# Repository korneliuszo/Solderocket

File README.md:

# Solderocket
Regular solder paste dispensers must be connected to compressed air which you can provide with huge compressor. As a maker I can not run a large compressor in my room because of its noise and footprint.

Stencils might be a solution but for small size PCB work they are too dirty and I don't like to touch the chemical solder paste with my hands and tools. It takes more time to clean up every time than apply it to the PCB.

That's why I decided to design a desktop solder paste dispenser that is clean, easy to use and small in size. I call it Solderocket.

Using the rotary knobs, the time and pressure can be set so that the right dot size can be selected for each type of solder paste.

This device is indispensable when working with SMD on a regular basis. SMD paste can be dosed very accurately and quickly. Adhesives can be used in addition to SMD paste.

# Specifications
* No Compressor needed. Works with Co2 cartridges.
* Adjustable pressure 0-60 psi 
* Adjustable timing from 50 millisecond up to trigger release.
* Ergonomic Injector hand tool
* Dimensions : 155 x 120 x 75 mm
* Weight : 770 gr  (without packaging)
* Works with 12V DC adapter

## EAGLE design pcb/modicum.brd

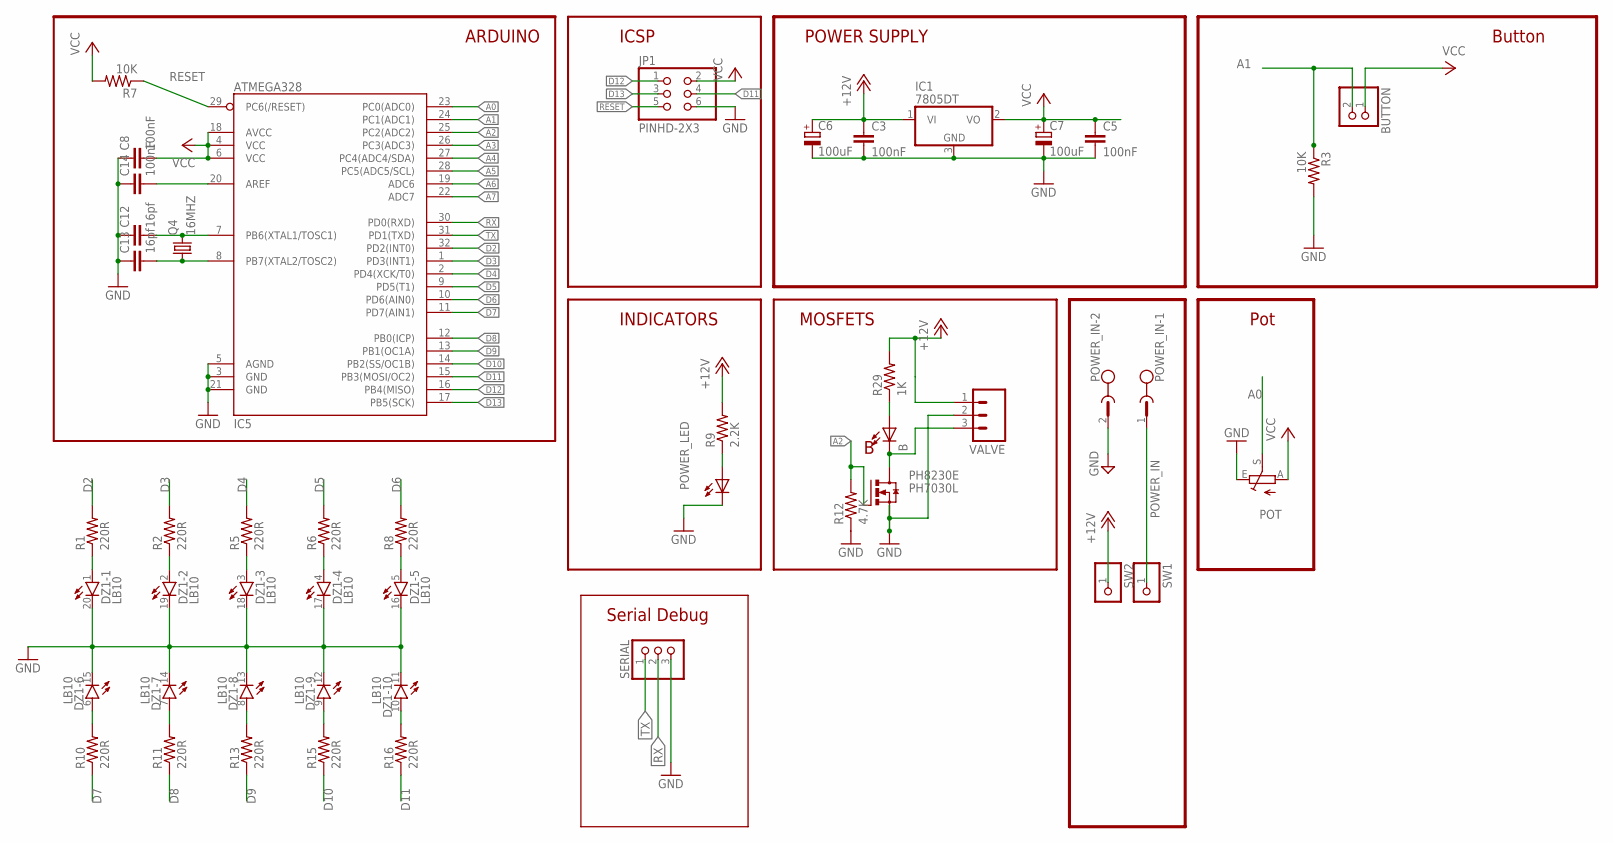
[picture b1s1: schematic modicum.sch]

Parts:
B: LED0805; LED-0805
BUTTON: PINHD-1X2; 1X02
C3, C5, C8, C14: 100nF; 0805
C6, C7: 100uF; E3,5-8
C12, C13: 16pf; 0805
DZ1: LB10
IC1: 7805DT; TO252
IC5: ATMEGA328; TQFP32-08
JP1: PINHD-2X3; 2X03
PH8230E: PH7030L; SOT669
POT: TRIM_EU-CIP20C-6MM; CIP20C-6MM
POWER_IN: MST2V; MSTBV2
POWER_LED: LED0805; LED-0805
Q4: 16MHZ; HC49/S
R1, R2, R5, R6, R8, R10, R11, R13, R15, R16: 220R; 0805
R3, R7: 10K; 0805
R9: 2.2K; 0805
R12: 4.7K; 0805
R29: 1K; 0805
SERIAL: PINHD-1X3; 1X03
SW1, SW2: PINHD-1X1; 1X01
VALVE: M03; 03P

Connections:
+12V: C3.1, C6.+, IC1.1 (VI), R9.2, R29.2, SW2.1, VALVE.1
A0: IC5.23 (PC0(ADC0)), POT.S
A1: BUTTON.2, IC5.24 (PC1(ADC1)), R3.1
A2: IC5.25 (PC2(ADC2)), PH8230E.4 (G), R12.2
A3: IC5.26 (PC3(ADC3))
A4: IC5.27 (PC4(ADC4/SDA))
A5: IC5.28 (PC5(ADC5/SCL))
A6: IC5.19 (ADC6)
A7: IC5.22 (ADC7)
BPWR: B.C, PH8230E.MB (D), VALVE.3
D2: IC5.32 (PD2(INT0)), R1.2
D3: IC5.1 (PD3(INT1)), R2.2
D4: IC5.2 (PD4(XCK/T0)), R5.2
D5: IC5.9 (PD5(T1)), R6.2
D6: IC5.10 (PD6(AIN0)), R8.2
D7: IC5.11 (PD7(AIN1)), R10.1
D8: IC5.12 (PB0(ICP)), R11.1
D9: IC5.13 (PB1(OC1A)), R13.1
D10: IC5.14 (PB2(SS/OC1B)), R15.1
D11: IC5.15 (PB3(MOSI/OC2)), JP1.4, R16.1
D12: IC5.16 (PB4(MISO)), JP1.1
D13: IC5.17 (PB5(SCK)), JP1.3
GND: C3.2, C5.2, C6.-, C7.-, C8.1, C12.1, C13.1, C14.1, DZ1.11 (C), DZ1.12 (C), DZ1.13 (C), DZ1.14 (C), DZ1.15 (C), DZ1.16 (C), DZ1.17 (C), DZ1.18 (C), DZ1.19 (C), DZ1.20 (C), IC1.3 (GND), IC5.3 (GND), IC5.5 (AGND), IC5.21 (GND), JP1.6, PH8230E.1 (S), PH8230E.2 (S), PH8230E.3 (S), POT.E, POWER_IN.2, POWER_LED.C, R3.2, R12.1, SERIAL.3, VALVE.2
unnamed: DZ1.1 (A), R1.1
unnamed: DZ1.2 (A), R2.1
unnamed: DZ1.3 (A), R5.1
unnamed: DZ1.4 (A), R6.1
unnamed: DZ1.5 (A), R8.1
unnamed: DZ1.6 (A), R10.2
unnamed: DZ1.7 (A), R11.2
unnamed: DZ1.8 (A), R13.2
unnamed: DZ1.9 (A), R15.2
unnamed: DZ1.10 (A), R16.2
unnamed: C14.2, IC5.20 (AREF)
unnamed: POWER_LED.A, R9.1
unnamed: C12.2, IC5.7 (PB6(XTAL1/TOSC1)), Q4.2
unnamed: C13.2, IC5.8 (PB7(XTAL2/TOSC2)), Q4.1
unnamed: B.A, R29.1
POWER_IN: POWER_IN.1, SW1.1
RESET: IC5.29 (PC6(/RESET)), JP1.5, R7.1
RX: IC5.30 (PD0(RXD)), SERIAL.2
TX: IC5.31 (PD1(TXD)), SERIAL.1
VCC: BUTTON.1, C5.1, C7.+, C8.2, IC1.2 (VO), IC5.4 (VCC), IC5.6 (VCC), IC5.18 (AVCC), JP1.2, POT.A, R7.2

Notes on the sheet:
MOSFETS
ICSP
ARDUINO
INDICATORS
POWER SUPPLY
Button
Pot
Serial Debug

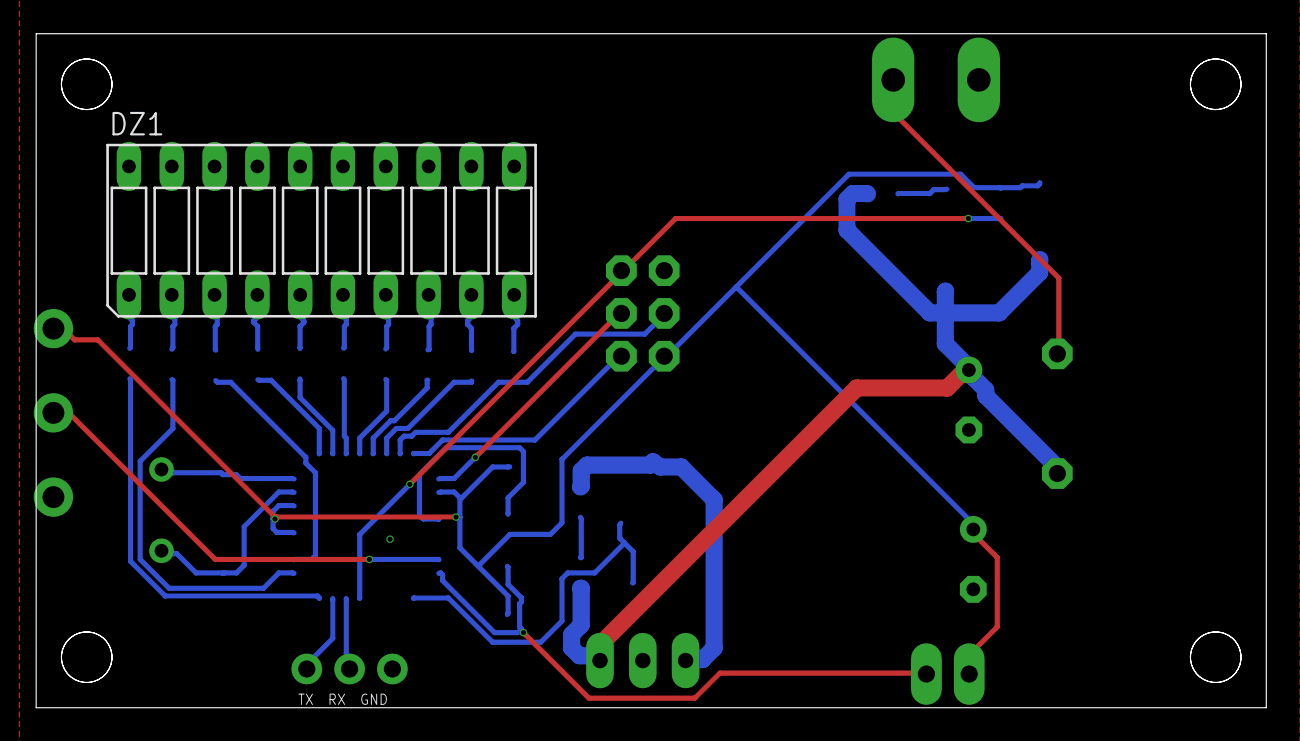
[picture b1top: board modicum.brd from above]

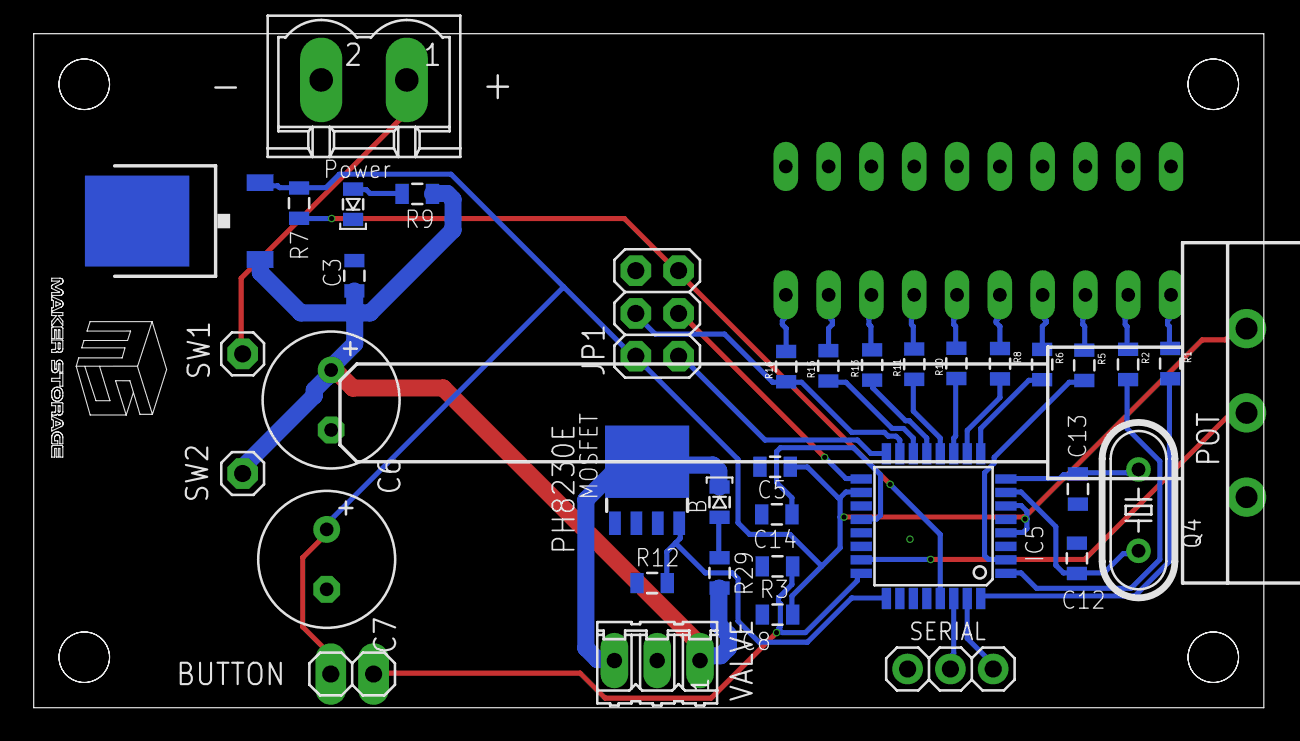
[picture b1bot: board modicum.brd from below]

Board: 2 copper layers, 73.0 x 40.0 mm, 38 parts (37 on the bottom side), 38 nets.

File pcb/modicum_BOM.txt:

Partlist exported from /home/nuri/electronics/modicum/pcb/modicum.sch at 14.10.2021 13:22

Qty Value     Device             Package    Parts                                       Description                              CATEGORY  DESCRIPTION MANUFACTURER MF MPN OC_FARNELL OC_NEWARK OPERATING_TEMP PART_STATUS POPULARITY ROHS_COMPLIANT SERIES SUB-CATEGORY THERMALLOSS TYPE
2             LED0805            LED-0805   B, POWER_LED                                LEDs                                                                                                                                                                                             
1             M03                03P        VALVE                                       AMP QUICK CONNECTOR                                                                unknown    unknown                              12                                                            
2             PINHD-1X1          1X01       SW1, SW2                                    PIN HEADER                                                                                                                         64                                                            
1             PINHD-1X2          1X02       BUTTON                                      PIN HEADER                                                                                                                         98                                                            
1             PINHD-1X3          1X03       SERIAL                                      PIN HEADER                                                                                                                                                                                       
1             TRIM_EU-CIP20C-6MM CIP20C-6MM POT                                         POTENTIOMETER                                                                                                                                                                                    
4   100nF     CAP0805            0805       C3, C5, C8, C14                             Capacitor                                                                                                                                                                                        
2   100uF     CPOL-EUE3.5-8      E3,5-8     C6, C7                                      POLARIZED CAPACITOR, European symbol                                                                                                                                                             
2   10K       RESISTOR           0805       R3, R7                                      Resistor                                                                                                                                                                                         
1   16MHZ     CRYSTALHC49S       HC49/S     Q4                                          CRYSTAL                                                                                                                                                                                          
2   16pf      CAP0805            0805       C12, C13                                    Capacitor                                                                                                                                                                                        
1   1K        RESISTOR           0805       R29                                         Resistor                                                                                                                                                                                         
1   2.2K      RESISTOR           0805       R9                                          Resistor                                                                                                                                                                                         
10  220R      RESISTOR           0805       R1, R2, R5, R6, R8, R10, R11, R13, R15, R16 Resistor                                                                                                                                                                                         
1   4.7K      RESISTOR           0805       R12                                         Resistor                                                                                                                                                                                         
1   7805DT    7805DT             TO252      IC1                                         Positive VOLTAGE REGULATOR                                                                                                                                                                       
1   ATMEGA328 ATMEGA168          TQFP32-08  IC5                                                                                                                                                                                                                                          
1   LB10      LB10               LB10       DZ1                                         LED BLOCK                                                                                                                          1                                                             
1   MST2V     MST2V              MSTBV2     POWER_IN                                    PHOENIX                                                                                                                                                                                          
1   PH7030L   PH7030L            SOT669     PH8230E                                     N-channel TrenchMOS (TM) logic level FET                                                                                                                                                         
1   PINHD-2X3 PINHD-2X3          2X03       JP1                                         PIN HEADER                               CONNECTOR                                                                                                                  PIN-HEADER

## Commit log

2021-11-04 3D Files
2021-11-04 Readme
2021-11-04 Readme 2
2021-11-04 Readme 3
2021-11-04 Readme 4
2021-11-04 Readme 5
2021-11-04 Readme 6
2021-11-23 It compiles
2021-11-23 Disable digital input on ADC input
2021-11-23 Include forgotten binaries
2022-01-21 Remove binaries
2022-01-21 Proper CPU model
2022-01-21 Make better snake
